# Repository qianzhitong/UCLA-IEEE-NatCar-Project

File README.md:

# UCLA-IEEE-NatCar-Project
IEEE club at UCLA's NatCar Project (2016)

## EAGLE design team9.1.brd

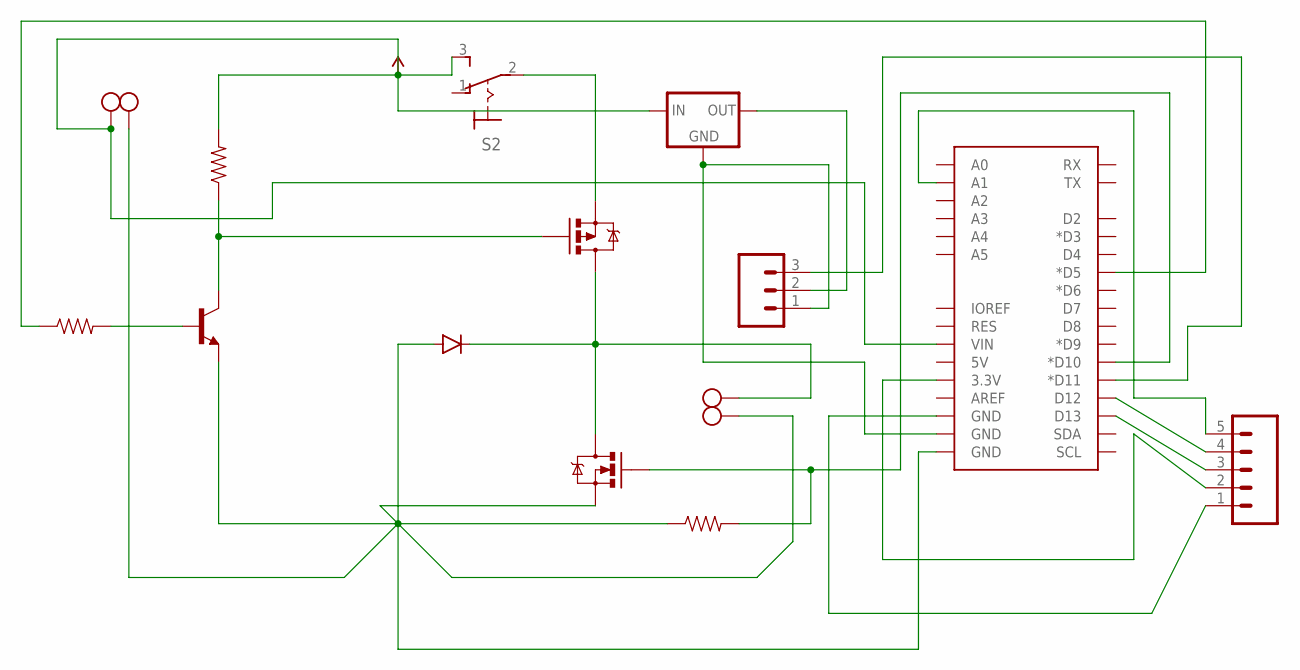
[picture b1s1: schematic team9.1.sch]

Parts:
D1: DIODEKIT; DIODE-1N4148-KIT
J1: ARDUINO_R3_SHIELD; UNO_R3_SHIELD
J2: M05LOCK; 1X05_LOCK
J4: M03LOCK; 1X03_LOCK
Q1: MOSFET-PCHANNELFQP27P06; TO220V
Q2: TRANSISTOR_NPNBC547; TO-92-AMMO
Q3: MOSFET-NCHANNELFQP30N06L; TO220V
R1, R2: 1000; AXIAL-0.3
R3: 10000; AXIAL-0.3
S2: TERMINAL_BLOCKM9040P_NATCAR; M9040P
U1: V_REG_78XXSINK; TO220-IGO
X1, X2: E-SWITCH; AK300/2

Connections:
unnamed: Q1.1 (G), Q2.1 (C), R2.P$1 (1)
unnamed: D1.A, J1.GND@0 (GND), Q2.3 (E), Q3.3 (S), R3.P$1 (1), X1.2, X2.2
unnamed: Q1.3 (S), S2.2
unnamed: D1.C, Q1.2 (D), Q3.2 (D), X1.1
unnamed: J1.D10 (*D10), Q3.1 (G), R3.P$2 (2)
unnamed: Q2.2 (B), R1.P$2 (2)
unnamed: J1.GND@1 (GND), J4.1, U1.GND
unnamed: J1.D11 (*D11), J4.3
unnamed: J1.GND@2 (GND), J2.1
unnamed: J1.D13, J2.3
unnamed: J1.D12, J2.4
unnamed: J1.A1, J2.5
unnamed: J1.3.3V, J2.2
unnamed: J4.2, U1.OUT
PWN: J1.D5 (*D5), R1.P$1 (1)
VDD: J1.VIN, R2.P$2 (2), S2.3 (S), U1.IN, X2.1

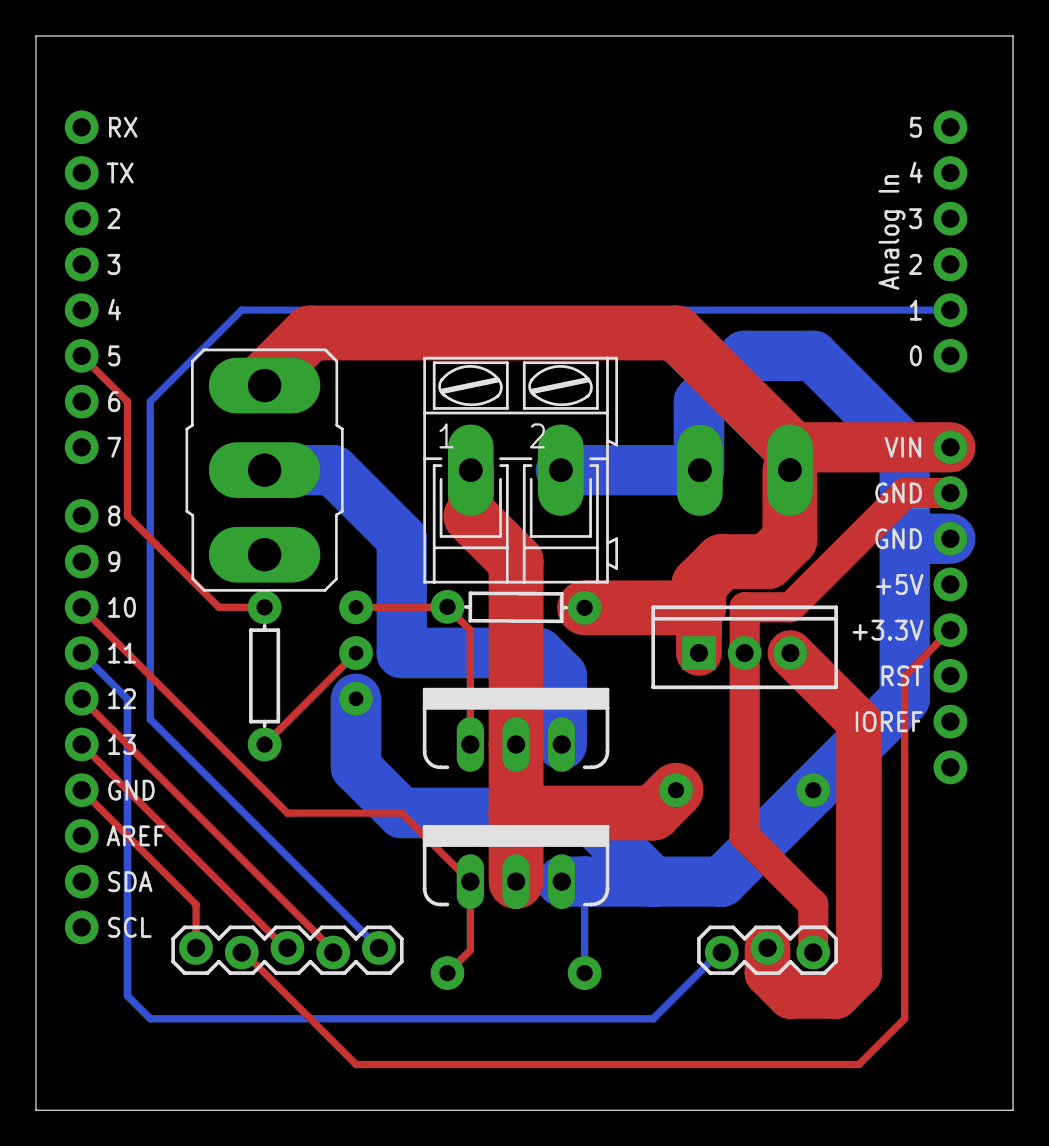
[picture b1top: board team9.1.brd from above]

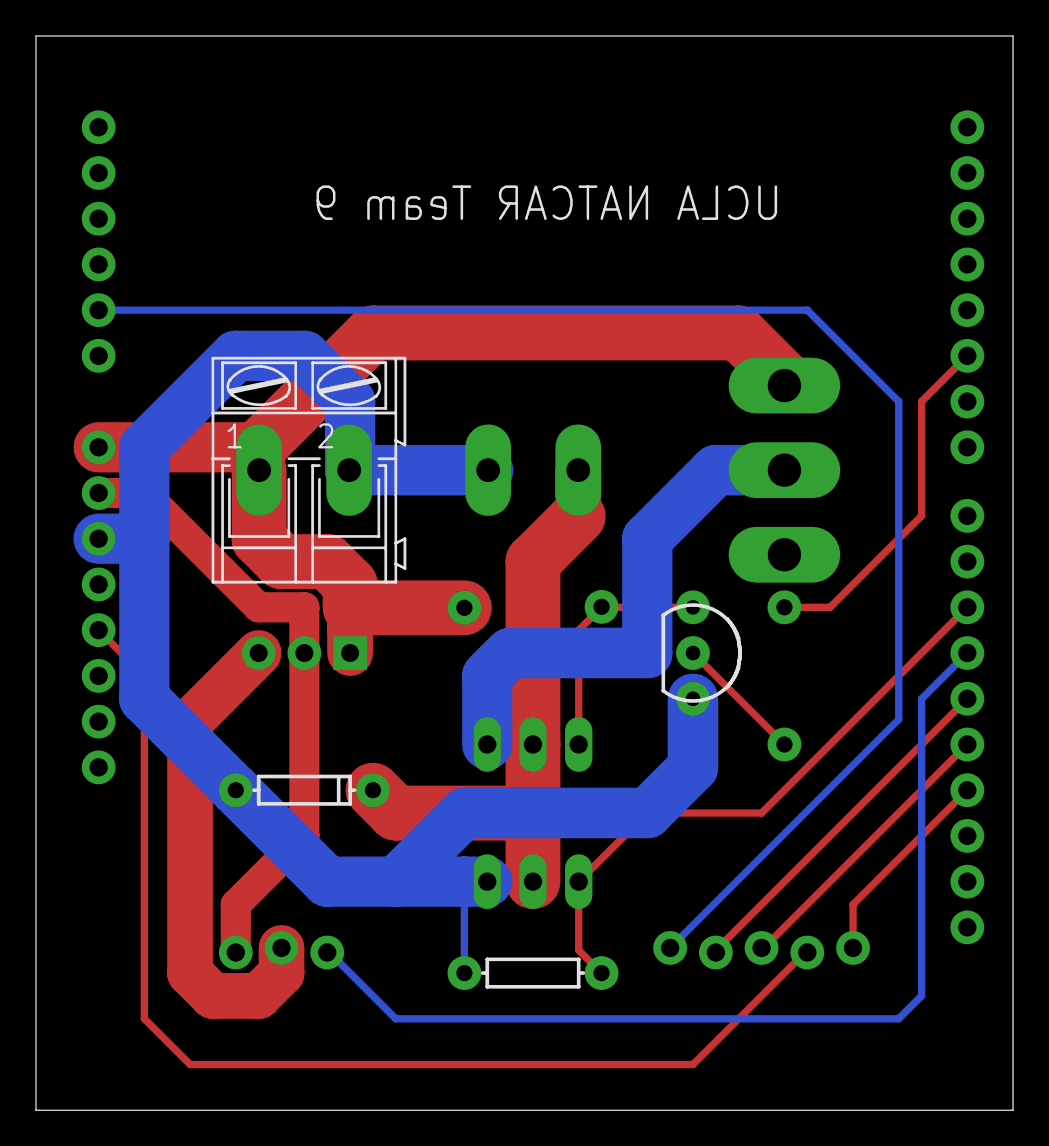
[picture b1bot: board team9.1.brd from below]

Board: 2 copper layers, 54.3 x 59.7 mm, 14 parts (4 on the bottom side), 16 nets.

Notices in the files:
parts and their libraries:
SparkFun-Boards: Licensing: Creative Commons ShareAlike 4.0 International - https://creativecommons.org/licenses/by-sa/4.0
